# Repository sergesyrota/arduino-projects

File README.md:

arduino-projects
================

My projects and libraries with Arduino

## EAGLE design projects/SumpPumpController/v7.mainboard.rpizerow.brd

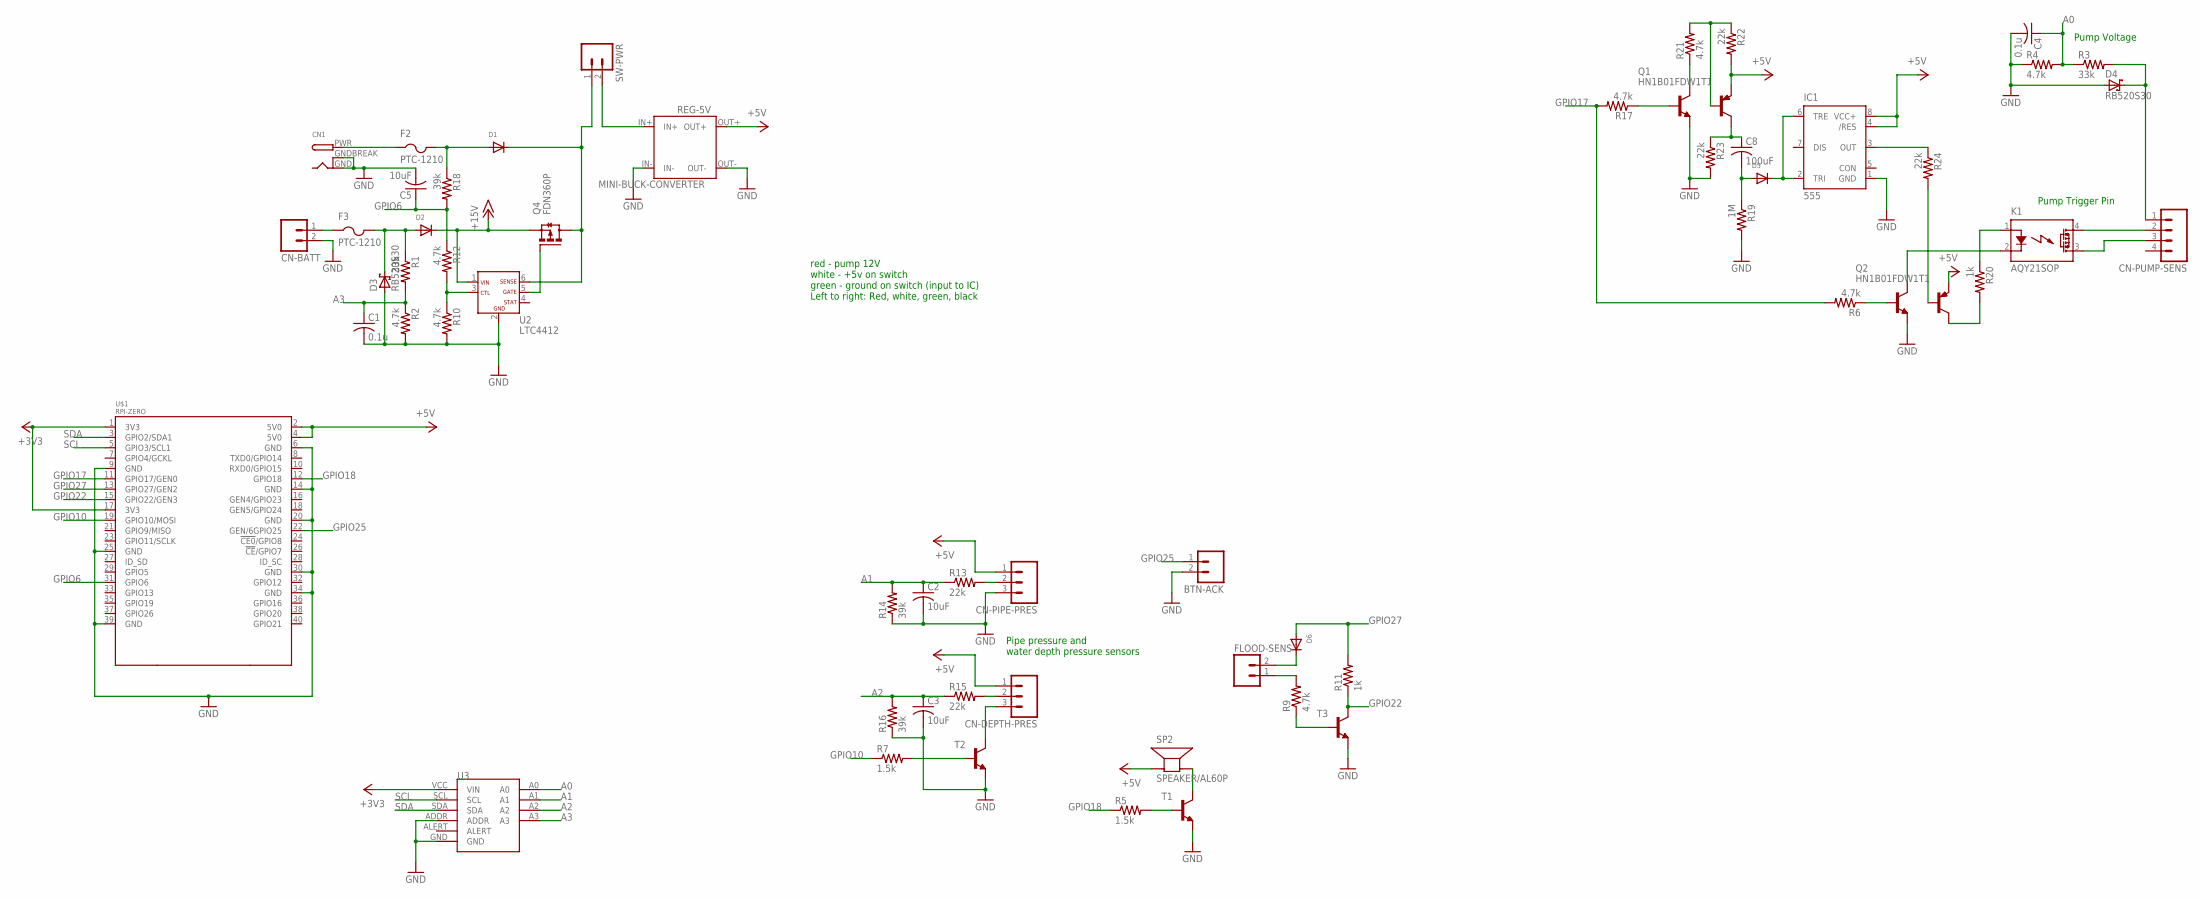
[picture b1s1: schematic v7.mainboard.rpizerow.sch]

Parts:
BTN-ACK: M02; 02P
C1, C4: 0.1u; C0603K
C2, C3, C5: 10uF; C0805K
C8: 100uF; C1210
CN1: DCBARRELPTH; DCJACK_2MM_PTH
CN-BATT: M02; 02P
CN-DEPTH-PRES: M03; 03P
CN-PIPE-PRES: M03; 03P
CN-PUMP-SENS: M04; 04P
D1, D2, D5, D6: DIODESOD-323F; SOD-323F
D3, D4: RB520S30; SOD523
F2, F3: PTC-1210; 1210
FLOOD-SENS: M02; 02P
IC1: 555; SO08
K1: AQY21SOP; SOP04
Q1, Q2: HN1B01FDW1T1; SOT23-6
Q4: FDN360P; SUPER-SOT3
R1, R3: 33k; R0603
R2, R4, R6, R9, R10, R12, R17, R21: 4.7k; R0603
R5, R7: 1.5k; R0603
R11, R20: 1k; R0603
R13, R15, R22, R23, R24: 22k; R0603
R14, R16, R18: 39k; R0603
R19: 1M; R0603
REG-5V: MINI-BUCK-CONVERTER
SP2: SPEAKER/AL60P; AL60P
SW-PWR: M02; 02P
T1, T2, T3: BC808-NPN-SOT23-BEC; SOT23-BEC
U2: LTC4412; SOT23-6
U3: GY-ADS1115THM; GY-ADS1115-THM
U$1: RPI-ZERO; RASPBERRYPI_BASTELSTUBE_V13_RASPI_BOARD_B+_FULL

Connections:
+3V3: U3.VCC (VIN), U$1.1 (3V3), U$1.17 (3V3)
+5V: CN-DEPTH-PRES.1, CN-PIPE-PRES.1, IC1.4 (/RES), IC1.8 (VCC+), Q1.1 (PNP-E), Q2.1 (PNP-E), R22.2, REG-5V.OUT+, SP2.1 (+), U$1.2 (5V0), U$1.4 (5V0)
+15V: D2.C, Q4.2 (S), U2.1 (VIN)
A0: C4.1, R3.1, R4.2, U3.A0
A1: C2.1, R13.1, R14.2, U3.A1
A2: C3.1, R15.1, R16.2, U3.A2
A3: C1.1, R1.2, R2.1, U3.A3
GND: BTN-ACK.2, C1.2, C2.2, C3.2, C4.2, C5.2, CN1.GND, CN1.GNDBREAK, CN-BATT.2, CN-PIPE-PRES.3, D3.2 (A), D4.2 (A), IC1.1 (GND), Q1.4 (NPN-E), Q2.4 (NPN-E), R2.2, R4.1, R10.2, R14.1, R16.1, R19.2, R23.2, REG-5V.IN-, REG-5V.OUT-, T1.E, T2.E, T3.E, U2.2 (GND), U3.ADDR, U3.GND, U$1.6 (GND), U$1.9 (GND), U$1.14 (GND), U$1.20 (GND), U$1.25 (GND), U$1.30 (GND), U$1.34 (GND), U$1.39 (GND)
GPIO6: C5.1, R12.1, R18.2, U$1.31 (GPIO6)
GPIO10: R7.1, U$1.19 (GPIO10/MOSI)
GPIO17: R6.2, R17.2, U$1.11 (GPIO17/GEN0)
GPIO18: R5.1, U$1.12 (GPIO18)
GPIO22: R11.1, T3.C, U$1.15 (GPIO22/GEN3)
GPIO25: BTN-ACK.1, U$1.22 (GEN/6GPIO25)
GPIO27: D6.A, R11.2, U$1.13 (GPIO27/GEN2)
unnamed: Q4.1 (G), U2.5 (GATE)
unnamed: R10.1, R12.2, U2.3 (CTL)
unnamed: SP2.2 (-), T1.C
unnamed: CN-PUMP-SENS.1, D4.1 (K), R3.2
unnamed: REG-5V.IN+, SW-PWR.2
unnamed: Q2.5 (NPN-B), R6.1
unnamed: CN-DEPTH-PRES.2, R15.2
unnamed: R5.2, T1.B
unnamed: CN-DEPTH-PRES.3, T2.C
unnamed: CN-PIPE-PRES.2, R13.2
unnamed: R9.1, T3.B
unnamed: Q1.5 (NPN-B), R17.1
unnamed: D2.A, D3.1 (K), F3.2, R1.1
unnamed: R7.2, T2.B
unnamed: CN-BATT.1, F3.1
unnamed: D1.C, Q4.3 (D), SW-PWR.1, U2.6 (SENSE)
unnamed: CN1.PWR, F2.1
unnamed: D1.A, F2.2, R18.1
unnamed: Q1.3 (NPN-C), R21.1
unnamed: FLOOD-SENS.1, R9.2
unnamed: D6.C, FLOOD-SENS.2
unnamed: K1.1 (A), R20.1
unnamed: Q1.2 (PNP-B), R21.2, R22.1
unnamed: C8.1, Q1.6 (PNP-C), R23.1
unnamed: C8.2, D5.A, R19.1
unnamed: D5.C, IC1.2 (TRI), IC1.6 (TRE)
unnamed: IC1.3 (OUT), R24.1
unnamed: K1.2 (K), Q2.3 (NPN-C)
unnamed: Q2.6 (PNP-C), R20.2
unnamed: Q2.2 (PNP-B), R24.2
unnamed: CN-PUMP-SENS.2, K1.4 (DS1)
unnamed: CN-PUMP-SENS.3, K1.3 (DS2)
SCL: U3.SCL, U$1.5 (GPIO3/SCL1)
SDA: U3.SDA, U$1.3 (GPIO2/SDA1)

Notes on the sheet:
Pump Voltage
Pump Trigger Pin
Pipe pressure and water depth pressure sensors
red - pump 12V white - +5v on switch green - ground on switch (input to IC) Left to right: Red, white, green, black

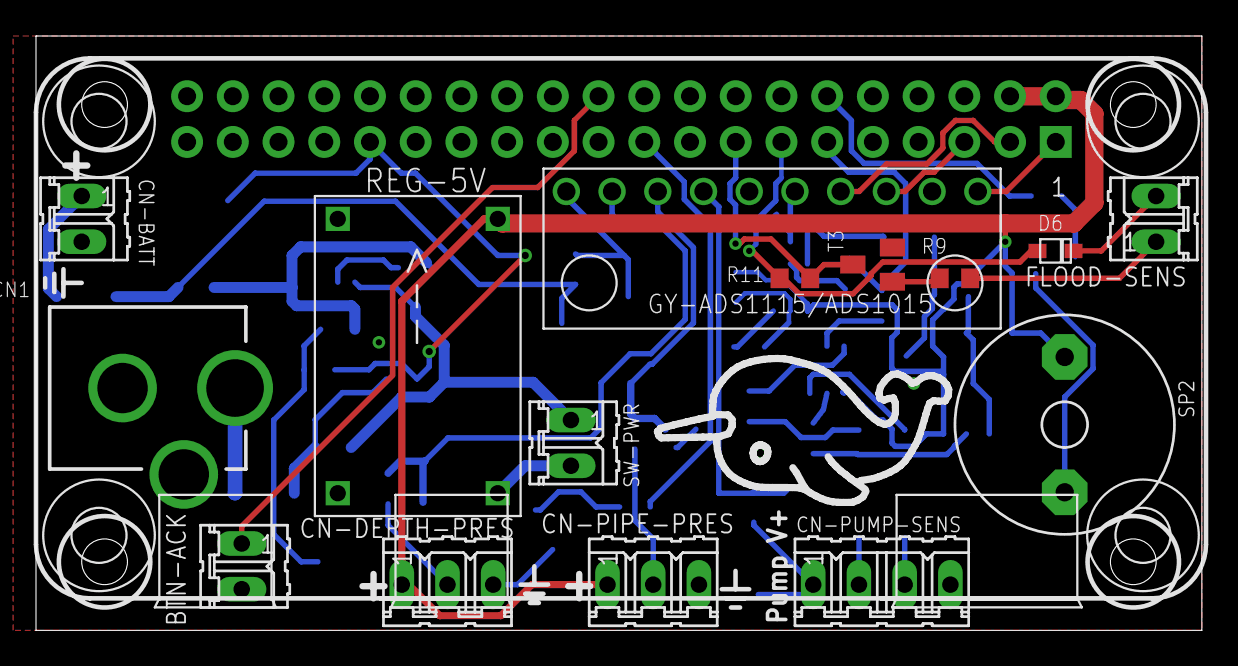
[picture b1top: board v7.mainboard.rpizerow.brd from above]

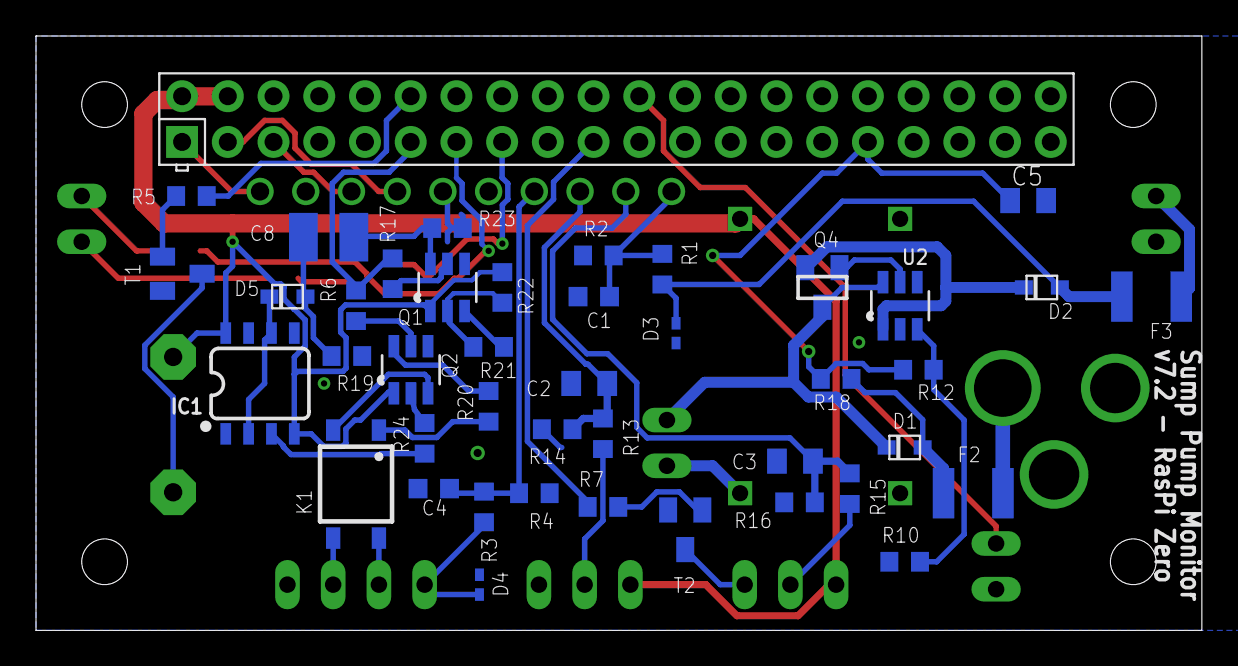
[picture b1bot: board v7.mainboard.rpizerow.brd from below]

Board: 2 copper layers, 64.8 x 33.0 mm, 58 parts (42 on the bottom side), 49 nets.

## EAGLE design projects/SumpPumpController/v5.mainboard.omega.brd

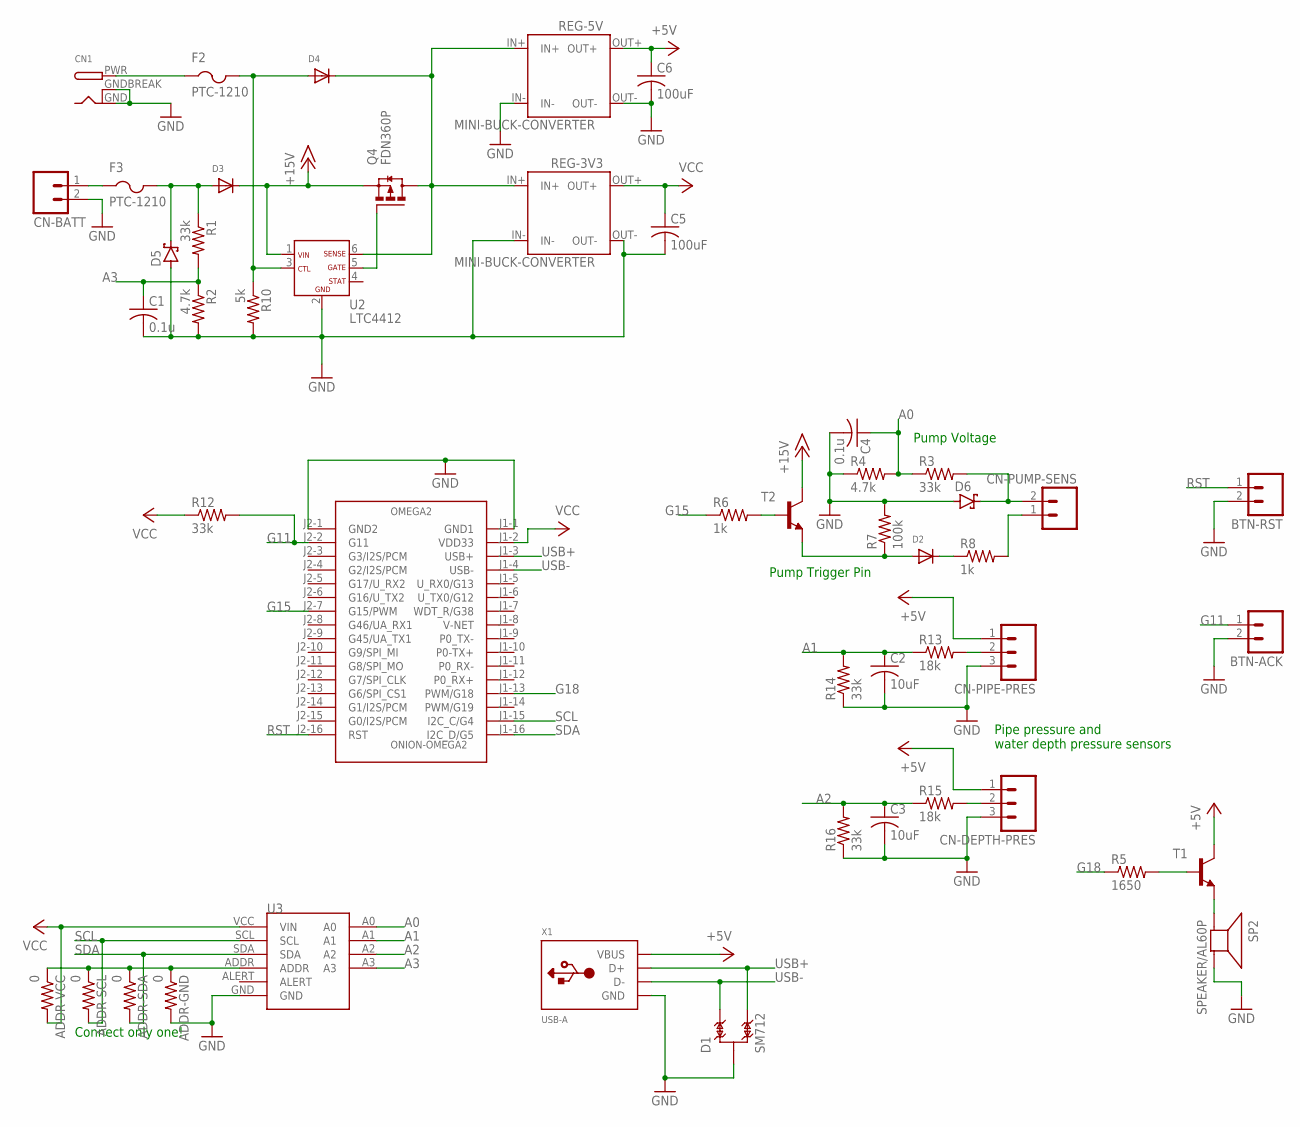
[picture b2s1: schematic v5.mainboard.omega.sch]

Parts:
ADDR-GND: 0; R0603
ADDR-SCL: 0; R0603
ADDR-SDA: 0; R0603
ADDR-VCC: 0; R0603
BTN-ACK: M02; 02P
BTN-RST: M02; 02P
C1, C4: 0.1u; C0603K
C2, C3: 10uF; C0805K
C5, C6: 100uF; C2220K
CN1: DCBARRELPTH; DCJACK_2MM_PTH
CN-BATT: M02; 02P
CN-DEPTH-PRES: M03; 03P
CN-PIPE-PRES: M03; 03P
CN-PUMP-SENS: M02; 02P
D1: SM712; SOT23-3
D2, D3, D4: DIODESMA; SMADIODE
D5, D6: SCHOTTKY-DIODESMC; SMC
F2, F3: PTC-1210; 1210
OMEGA2: ONION-OMEGA2; ONION-2MM-2X16
Q4: FDN360P; SUPER-SOT3
R1, R3, R12, R14, R16: 33k; R0603
R2, R4: 4.7k; R0603
R5: 1650; R0603
R6, R8: 1k; R0603
R7: 100k; R0603
R10: 5k; R0603
R13, R15: 18k; R0603
REG-3V3, REG-5V: MINI-BUCK-CONVERTER
SP2: SPEAKER/AL60P; AL60P
T1, T2: BC808-NPN-SOT23-BEC; SOT23-BEC
U2: LTC4412; SOT23-6
U3: GY-ADS1115THM; GY-ADS1115-THM
X1: USB-A; MOLEX_480371000

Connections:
+5V: C6.1, CN-DEPTH-PRES.1, CN-PIPE-PRES.1, REG-5V.OUT+, T1.C, X1.1 (VBUS)
+15V: D3.C, Q4.2 (S), T2.C, U2.1 (VIN)
A0: C4.1, R3.1, R4.2, U3.A0
A1: C2.1, R13.1, R14.2, U3.A1
A2: C3.1, R15.1, R16.2, U3.A2
A3: C1.1, R1.2, R2.1, U3.A3
G11: BTN-ACK.1, OMEGA2.J2-2 (G11), R12.2
G15: OMEGA2.J2-7 (G15/PWM), R6.1
G18: OMEGA2.J1-13 (PWM/G18), R5.1
GND: ADDR-GND.2, BTN-ACK.2, BTN-RST.2, C1.2, C2.2, C3.2, C4.2, C5.2, C6.2, CN1.GND, CN1.GNDBREAK, CN-BATT.2, CN-DEPTH-PRES.3, CN-PIPE-PRES.3, D1.3, D5.A, D6.A, OMEGA2.J1-1 (GND1), OMEGA2.J2-1 (GND2), R2.2, R4.1, R7.2, R10.2, R14.1, R16.1, REG-3V3.IN-, REG-3V3.OUT-, REG-5V.IN-, REG-5V.OUT-, SP2.2 (-), U2.2 (GND), U3.GND, X1.4 (GND)
unnamed: Q4.1 (G), U2.5 (GATE)
unnamed: ADDR-GND.1, ADDR-SCL.1, ADDR-SDA.1, ADDR-VCC.1, U3.ADDR
unnamed: CN-PUMP-SENS.2, D6.C, R3.2
unnamed: D2.C, R8.1
unnamed: CN-PUMP-SENS.1, R8.2
unnamed: CN-DEPTH-PRES.2, R15.2
unnamed: R5.2, T1.B
unnamed: SP2.1 (+), T1.E
unnamed: CN-PIPE-PRES.2, R13.2
unnamed: R6.2, T2.B
unnamed: D3.A, D5.C, F3.2, R1.1
unnamed: D2.A, R7.1, T2.E
unnamed: CN-BATT.1, F3.1
unnamed: D4.C, Q4.3 (D), REG-3V3.IN+, REG-5V.IN+, U2.6 (SENSE)
unnamed: CN1.PWR, F2.1
unnamed: D4.A, F2.2, R10.1, U2.3 (CTL)
RST: BTN-RST.1, OMEGA2.J2-16 (RST)
SCL: ADDR-SCL.2, OMEGA2.J1-15 (I2C_C/G4), U3.SCL
SDA: ADDR-SDA.2, OMEGA2.J1-16 (I2C_D/G5), U3.SDA
USB+: D1.1, OMEGA2.J1-3 (USB+), X1.3 (D+)
USB-: D1.2, OMEGA2.J1-4 (USB-), X1.2 (D-)
VCC: ADDR-VCC.2, C5.1, OMEGA2.J1-2 (VDD33), R12.1, REG-3V3.OUT+, U3.VCC (VIN)

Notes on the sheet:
Pump Voltage
Pump Trigger Pin
Pipe pressure and water depth pressure sensors
Connect only one!

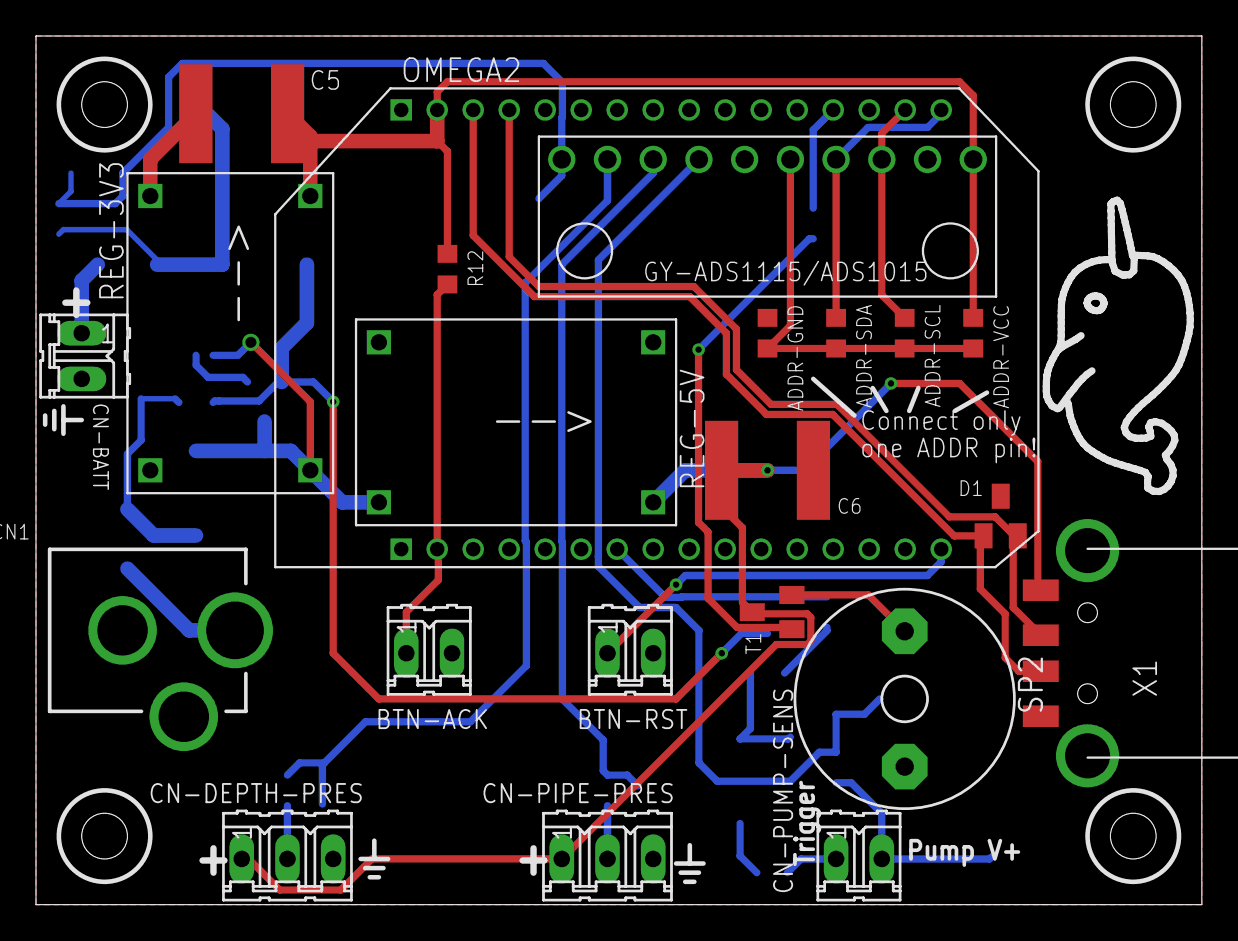
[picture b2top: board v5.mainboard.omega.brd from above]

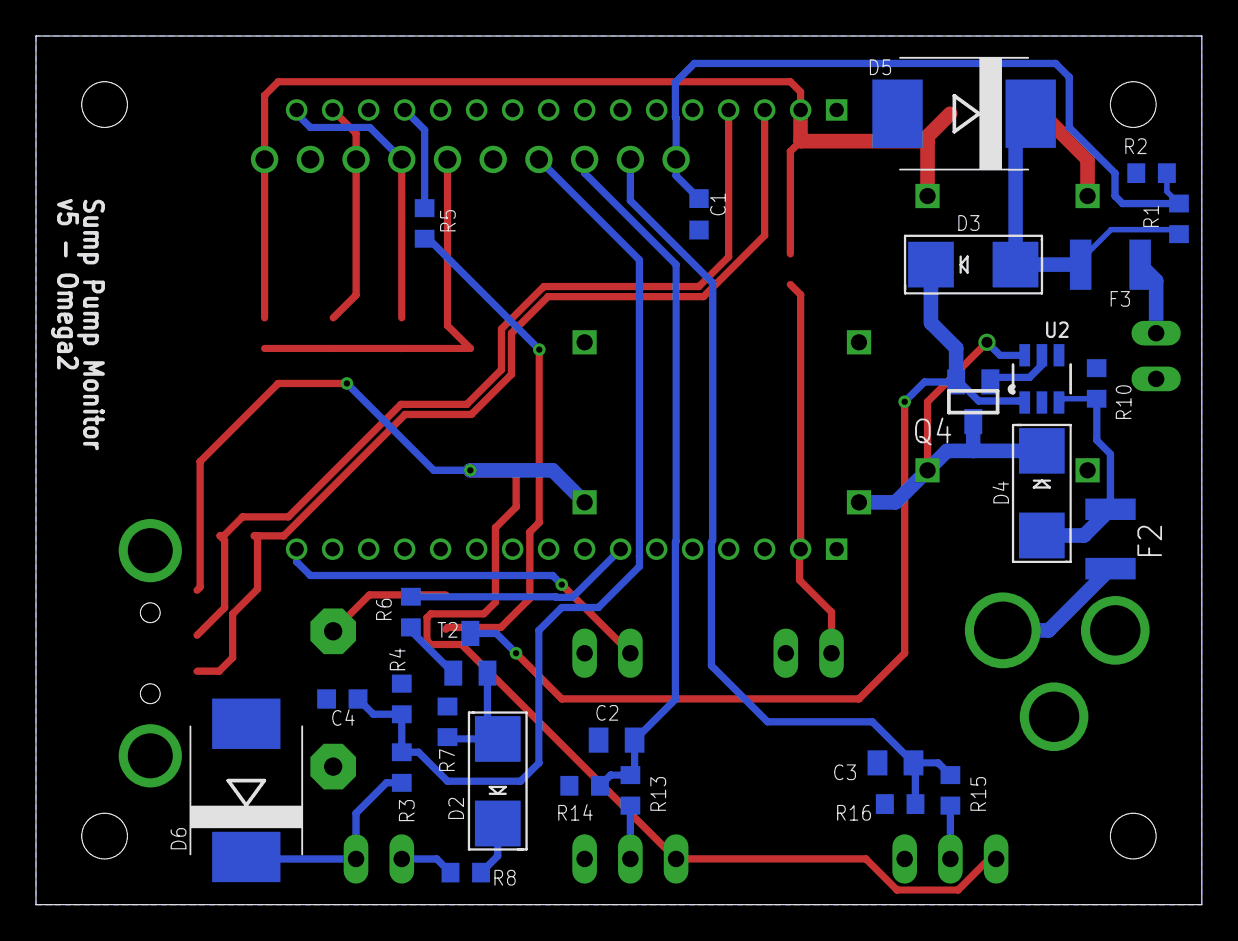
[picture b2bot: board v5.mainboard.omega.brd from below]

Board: 2 copper layers, 64.8 x 48.3 mm, 49 parts (27 on the bottom side), 32 nets.

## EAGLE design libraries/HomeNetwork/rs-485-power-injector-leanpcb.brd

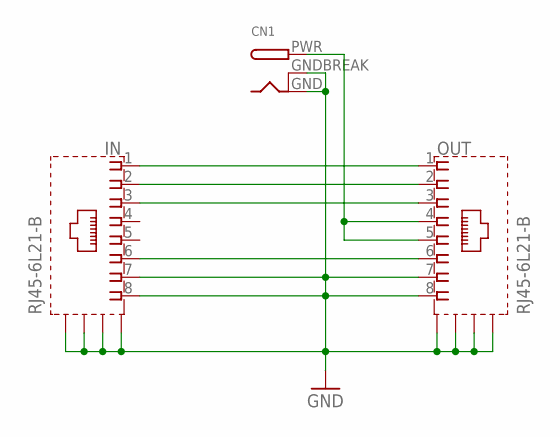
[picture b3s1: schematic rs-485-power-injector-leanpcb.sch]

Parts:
CN1: DCBARRELPTH; DCJACK_2MM_PTH
IN: RJ45-6L21-B; RJ45-SHIELD1
OUT: RJ45-6L21-B; RJ45-SHIELD1

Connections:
GND: CN1.GND, CN1.GNDBREAK, IN.7, IN.8, IN.S1 (S), IN.S2 (S), IN.S3 (S), IN.S4 (S), OUT.7, OUT.8, OUT.S1 (S), OUT.S2 (S), OUT.S3 (S), OUT.S4 (S)
unnamed: IN.1, OUT.1
unnamed: IN.2, OUT.2
unnamed: IN.3, OUT.3
unnamed: IN.6, OUT.6
unnamed: CN1.PWR, OUT.4, OUT.5

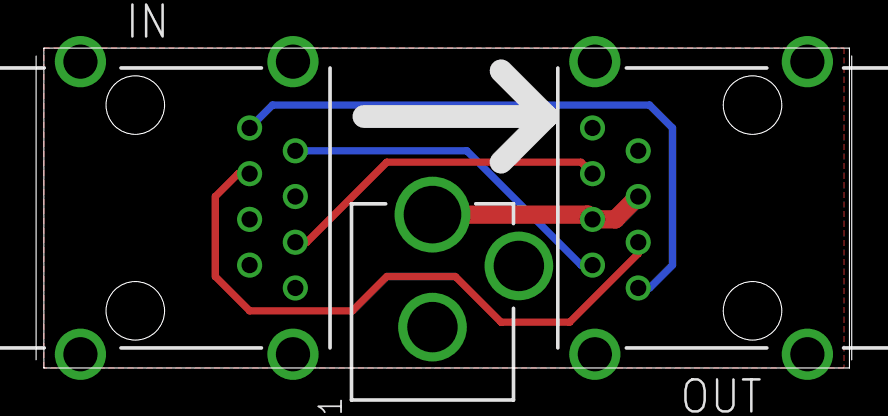
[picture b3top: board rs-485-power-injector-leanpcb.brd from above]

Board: 2 copper layers, 45.3 x 17.8 mm, 3 parts (0 on the bottom side), 6 nets.

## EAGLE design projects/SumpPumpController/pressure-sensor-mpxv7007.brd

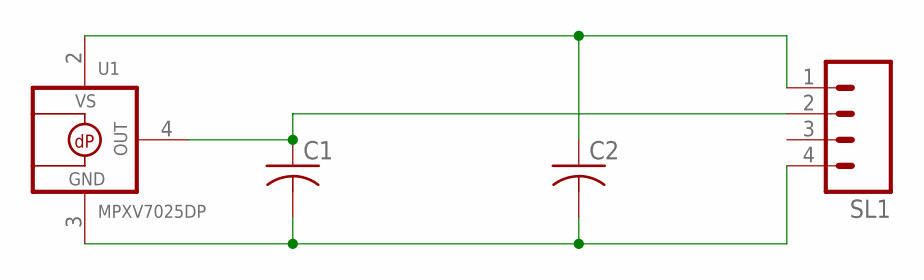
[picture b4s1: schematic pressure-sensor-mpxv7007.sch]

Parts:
C1: C-USC0805; C0805
C2: C-USC0603; C0603
SL1: M04; 04P
U1: MPXV7025DP; SOP8-1351

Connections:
GND: C1.2, C2.2, SL1.4, U1.3 (GND)
unnamed: C2.1, SL1.1, U1.2 (VS)
unnamed: C1.1, SL1.2, U1.4 (+VOUT)

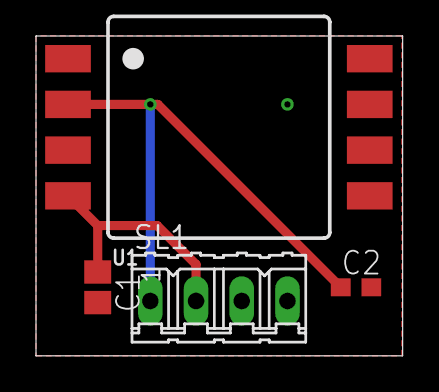
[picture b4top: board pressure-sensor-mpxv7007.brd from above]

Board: 2 copper layers, 20.4 x 17.8 mm, 4 parts (0 on the bottom side), 3 nets.

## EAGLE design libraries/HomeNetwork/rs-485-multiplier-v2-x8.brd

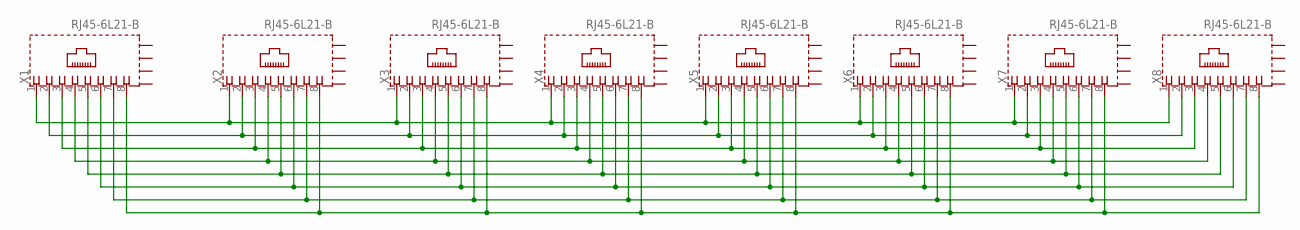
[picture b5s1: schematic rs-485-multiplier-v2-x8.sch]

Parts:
X1, X2, X3, X4, X5, X6, X7, X8: RJ45-6L21-B; RJ45-SHIELD1

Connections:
unnamed: X1.1, X2.1, X3.1, X4.1, X5.1, X6.1, X7.1, X8.1
unnamed: X1.2, X2.2, X3.2, X4.2, X5.2, X6.2, X7.2, X8.2
unnamed: X1.3, X2.3, X3.3, X4.3, X5.3, X6.3, X7.3, X8.3
unnamed: X1.4, X2.4, X3.4, X4.4, X5.4, X6.4, X7.4, X8.4
unnamed: X1.5, X2.5, X3.5, X4.5, X5.5, X6.5, X7.5, X8.5
unnamed: X1.6, X2.6, X3.6, X4.6, X5.6, X6.6, X7.6, X8.6
unnamed: X1.7, X2.7, X3.7, X4.7, X5.7, X6.7, X7.7, X8.7
unnamed: X1.8, X2.8, X3.8, X4.8, X5.8, X6.8, X7.8, X8.8

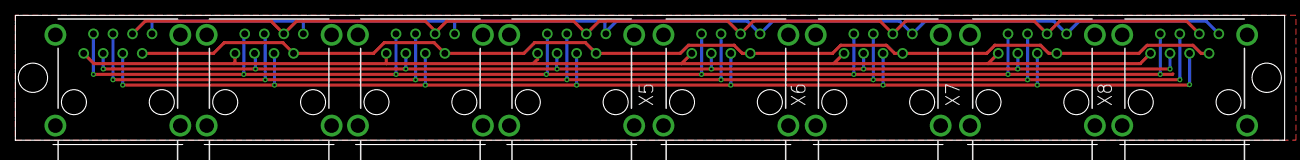
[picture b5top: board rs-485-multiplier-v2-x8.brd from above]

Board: 2 copper layers, 165.1 x 16.8 mm, 8 parts (0 on the bottom side), 8 nets.

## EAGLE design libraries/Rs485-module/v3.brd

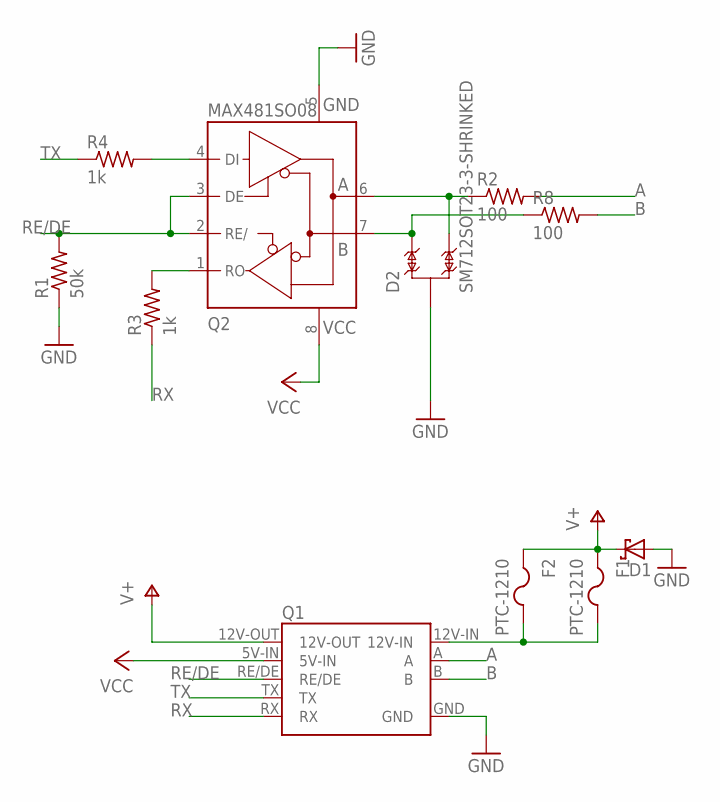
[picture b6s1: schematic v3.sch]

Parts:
D1: SCHOTTKY-DIODESMC; SMC
D2: SM712SOT23-3-SHRINKED; SOT23-3-SHRINKED
F1, F2: PTC-1210; 1210
Q1: RS485-ADAPTER0.05-CONNECTOR; RS485-ADAPTOR-05
Q2: MAX481SO08; SO08
R1: 50k; R0603
R2, R8: 100; R0603
R3, R4: 1k; R0603

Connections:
12V-IN: F1.2, F2.2, Q1.12V-IN
A: Q1.A, R2.2
B: Q1.B, R8.2
GND: D1.A, D2.3, Q1.GND, Q2.5 (GND), R1.1
unnamed: D2.2, Q2.7 (B), R8.1
unnamed: Q2.1 (RO), R3.2
unnamed: Q2.4 (DI), R4.2
unnamed: D2.1, Q2.6 (A), R2.1
RE/DE: Q1.RE/DE, Q2.2 (RE/), Q2.3 (DE), R1.2
RX: Q1.RX, R3.1
TX: Q1.TX, R4.1
V+: D1.C, F1.1, F2.1, Q1.12V-OUT
VCC: Q1.5V-IN, Q2.8 (+5V)

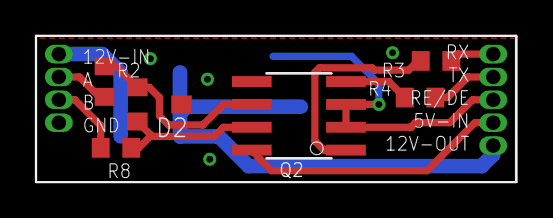
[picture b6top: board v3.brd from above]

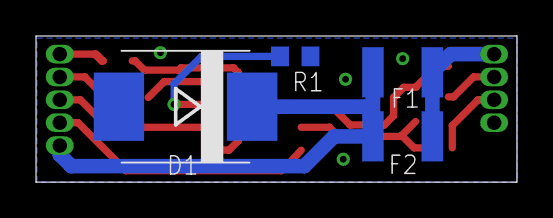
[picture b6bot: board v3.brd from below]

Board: 2 copper layers, 26.7 x 8.1 mm, 11 parts (4 on the bottom side), 13 nets.

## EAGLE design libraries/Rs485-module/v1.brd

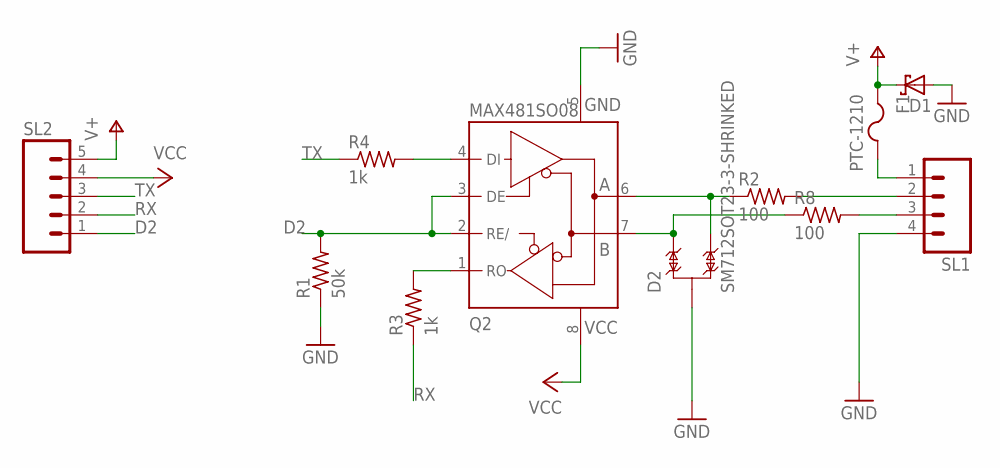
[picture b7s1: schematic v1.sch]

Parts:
D1: SCHOTTKY-DIODESMC; SMC
D2: SM712SOT23-3-SHRINKED; SOT23-3-SHRINKED
F1: PTC-1210; 1210
Q2: MAX481SO08; SO08
R1: 50k; R0603
R2, R8: 100; R0603
R3, R4: 1k; R0603
SL1: M04; 04P
SL2: M05; 05P

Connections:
D2: Q2.2 (RE/), Q2.3 (DE), R1.2, SL2.1
GND: D1.A, D2.3, Q2.5 (GND), R1.1, SL1.4
unnamed: F1.2, SL1.1
unnamed: D2.2, Q2.7 (B), R8.1
unnamed: Q2.1 (RO), R3.2
unnamed: Q2.4 (DI), R4.2
unnamed: R8.2, SL1.3
unnamed: R2.2, SL1.2
unnamed: D2.1, Q2.6 (A), R2.1
RX: R3.1, SL2.2
TX: R4.1, SL2.3
V+: D1.C, F1.1, SL2.5
VCC: Q2.8 (+5V), SL2.4

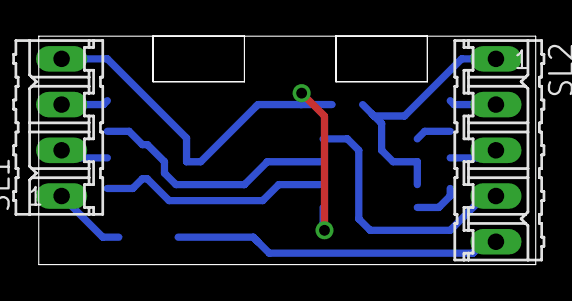
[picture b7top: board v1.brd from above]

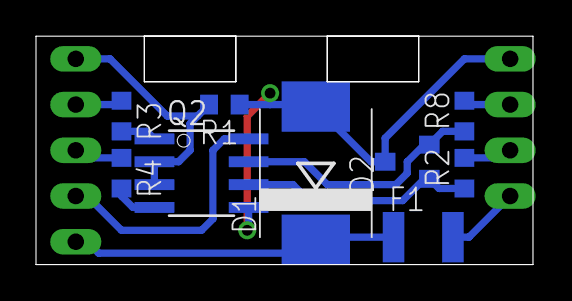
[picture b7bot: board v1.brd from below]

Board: 2 copper layers, 27.6 x 12.7 mm, 11 parts (9 on the bottom side), 13 nets.

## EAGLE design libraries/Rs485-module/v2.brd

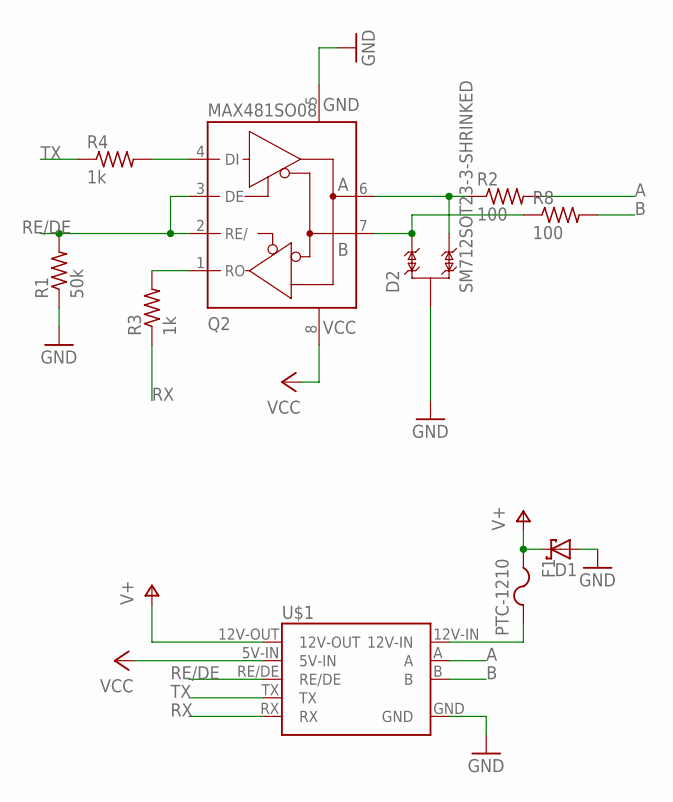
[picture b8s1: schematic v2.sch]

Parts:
D1: SCHOTTKY-DIODESMC; SMC
D2: SM712SOT23-3-SHRINKED; SOT23-3-SHRINKED
F1: PTC-1210; 1210
Q2: MAX481SO08; SO08
R1: 50k; R0603
R2, R8: 100; R0603
R3, R4: 1k; R0603
U$1: RS485-ADAPTER; RS485-ADAPTOR

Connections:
12V-IN: F1.2, U$1.12V-IN
A: R2.2, U$1.A
B: R8.2, U$1.B
GND: D1.A, D2.3, Q2.5 (GND), R1.1, U$1.GND
unnamed: D2.2, Q2.7 (B), R8.1
unnamed: Q2.1 (RO), R3.2
unnamed: Q2.4 (DI), R4.2
unnamed: D2.1, Q2.6 (A), R2.1
RE/DE: Q2.2 (RE/), Q2.3 (DE), R1.2, U$1.RE/DE
RX: R3.1, U$1.RX
TX: R4.1, U$1.TX
V+: D1.C, F1.1, U$1.12V-OUT
VCC: Q2.8 (+5V), U$1.5V-IN

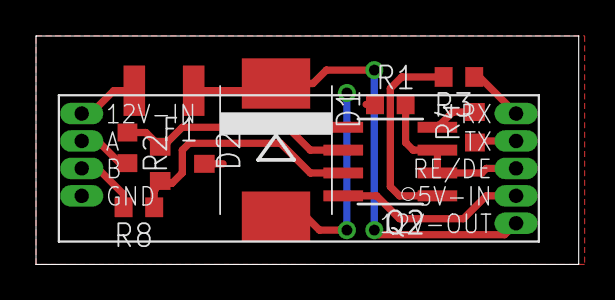
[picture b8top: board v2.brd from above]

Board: 2 copper layers, 30.1 x 12.7 mm, 10 parts (0 on the bottom side), 13 nets.

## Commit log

2013-07-21 Adding AutoHeadlights library
2013-07-21 Added notes on hardware components
2013-07-21 Added OneTouchLaneChange library
2013-07-21 Added my auto lights and one touch turn signal Arduino sketch
2013-07-23 Added readme to OneTouchLaneChange library
2013-08-03 Adding first draft of automated bath fan sketch, and humidity check class
2013-08-03 Cleaned up, added motion sensor support, implemented dummy reader for the switch
2013-08-04 Added data logger functionality
2013-08-14 Spelling correction for DHT11
2013-08-14 Bug fixes and adjustments based on field test
    - Fixed a bug that caused SD module to fail writing when trying to do so
    in constructor, before setup() is called (just removed header line
    check)
    - Changed triggeredHumidity check to short term average, as long term is
    too slow, and most likely we will not get back to that level fast enough
    - Added temperature in the log output
2013-08-15 Adjusted fail safe to 4 hours
2013-08-18 Adjusted headlight trigger values and time. Removed default overrides
2013-11-30 Adding Proximity sensor by device name
2013-11-30 Updates to proximity sensor
    Updated address storage method
    Removed debug serial output
    Delaying repeat ping if device is currently in range to avoid constant
    communication
2014-05-21 Adding sump pump controller files to the repo
2014-05-21 Renamed self test into controller in preparation of offloading all that logic there
2014-05-22 Updated instrumentation schematic to include voltage divider on the reference pin
2014-05-22 Added water main project
2014-05-23 Added pressure sensor functionality to the system, and changed from pump cycle reporting to number of seconds it was ON. Also added back self test, and added 24 hour minimum constraint.
2014-05-24 Adding automation protocol library v1
2014-05-24 Adding water main connection board
2014-05-24 Fixing a bug where when AC pump was ON when status was requested produced unexpected results (adding millis to seconds)
2014-05-26 Bug fixing in sump pump project: * Sending responses after action commands * Adding now() time to debug response * fixing long issues with self test time calculations * Delaying water level measureme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
2014-05-28 Added more debug output Adjusted instrumentation amplifier circuit to inlude ~1Hz filter, as turbulence in the sensor triggers false positives; Fixed a bug where self test time was not accounted for 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
2014-05-28 Added text to schematic for color coding of controll wire connection (WaterMain project)
2014-05-28 Starting to put together a tepmlate for Atmel based boards
2014-05-30 Adding first draft of WaterMain project
2014-05-30 Adding monitoring for when AC pump is on for too long to the sump pump project.
2014-06-01 Cleanup unused files in sump pump controller project.
2014-06-01 Added RS-485 splitter/multiplier board to the library
2014-06-02 Adjusted RS-485 splitter to ignore mounting holes to make room for routes
2014-06-03 Finished schematic of basic Atmel template. Kept all components but microcontroller out, as each board will have its own requirements, plus it would be challenging to keep all pieces from bumping int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
2014-06-08 Raising baud rate on the bus to max that ceramic resonator can reliably handle
2014-07-05 v1 of CPU module board finished
2014-07-07 Adding water meter counter and unit tests
2014-07-07 Moved unit tests into a sub-directory, hopefully they will not interfere with Arduino IDE build now.
2014-07-07 Just the counter version of water main code
2014-07-12 Added v2 of rs-485 multiplier board
2014-07-21 Finished v1 version of the board. Figured out that I have no way to control the valve from sensor. Built a fix-board to alleviate that issue. Just in case, threw down v2 with all components, but not 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
2014-07-21 Added config file to Water main, and moved analog sensor to that file as well.
2014-07-21 Added setup steps for valve directive pins, and fixed open/close pin mixup.
2014-07-27 Added valve control commands to water main project
2014-11-04 Added water main remote connection board v2 (with temperature and water leak probes)
2014-11-04 Updated water main sketch to add new v2 board, along with temperature and humidity probes.
2014-11-05 Refactored duplicate handling of errors in climate sensors for water meter module
2014-11-30 Updated PCB for CPU, increasing drill holes for some of the pins.
2014-11-30 Updated water main config, as valve connections got swapped
2014-11-30 Starting new project: bedroom HVAC balancer. Initial commit with first 2 versions of processing board
2014-11-30 Added kitchecn environment monitoring project
2014-11-30 Adding auto-led-light project in bedroom (to turn on LEDs after sunset
2014-12-21 Built hvac module, wireless probes, room controller boards. Wrote sketches for wireless probe, and some for AC sensors (still not tested, missing a few sensors themselves)
2014-12-21 Adding Pro Mini programmer shield
2014-12-21 Adding nrf24l01 bridge to rs485
2015-02-27 Added support for passing parameters to devices in the form of assertCommandStarts. This returns the rest of the command to be processed by the application.
2015-02-27 Adding explicit DHT22 to remote sensors RF module, and adding all sensor addresses to ac sensors.
2015-02-27 Adding power blinds project files.
2015-03-06 Adding v4 of sump pump controller. Includes standard Arduino Pro Mini connection, as well as few layers of protection. Although the drawing has a mistake, as cutout has wrong orientation :(
2015-03-06 Adjusted sump pump Arduino sketch for the new v4 board. TODO: fix reset alert handling; add butn-ack handling; implement eeprom configuration; re-enable buzzer pin; add last alert to memory (e.g. whe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
2015-03-06 Power blinds: adjusted to 9600 baud, added motor stop logic, added optical sensors readout. TODO: improve EEPROM storage; make baud rate adjustable; implement motion sensor; implement light sensor;
2015-03-07 Added improved alert handling, as well as ACK button to silence them. Alerts are now ranked in the order of priority. TODO: implement EEPROM configuration; re-enable buzzer pin.
2015-03-09 Sump pump controller: Moved more pins to include file; implemented EEPROM config; implemented config adjustment through rs485; Moved all sprintf templates into PROGMEM. TODO: enable buzzer when this 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
2015-03-09 Sump pump controller: changed serial interface to take baud rate from config.
2015-03-11 Added buzzer pin enable to config. Changed back from PROGMEM to standard variables for hardcoded text, as something was not working at all for most of those.
2015-03-13 Power Blinds: added configuration to dining controller, finished up controller logic
2015-03-14 Power blinds: updated dining controller to add optical sensor stop delay, switched to config baud rate, instead of hardcoded, fixed a bug with switch reading.
2015-03-14 Power blinds: refactoring dining controller to work off of proximity sensor only (without a need for tape marking); increased max configurable motor runtime.
2015-03-14 Power blinds: fixing config version increase...
2015-03-14 Power blinds: switched dining controller to differential reading, instead of proximity (for top position sensing). Adjusted defaults. switched to external pull-up.
2015-03-15 Power blinds: fixed a bug with knownBlindsPosition that was not allowing reversal of motion because known position was not reset when we start rolling
2015-03-15 Power blinds: adding external pull-up resistors for inputs, and adding TVS diode for RS-485
2015-03-15 Power blinds: Adjusted rollDown blinds threshold for dining controller.
2015-04-08 Fixing random hanging issues when rolling down the blinds
2015-04-26 Added getPressure command and fixed distance reading bug in SUmp Pump system.
2015-04-26 Added protection diode to motor control module in Power Blinds.
2015-04-26 Adjusting serial speed to 9600 for water main sensors.
2015-04-26 Adding nrf24l01 shield to the library
2015-04-26 Adjusted speed to 9600, and updated net address to be taken from confid, in HVAC balancer project.
2015-07-11 Adding RS-485 module board (including full protection circuit)
2016-02-09 Restored back/forward annotation of v3
2016-02-09 Modified v3 for large drill size (so that pin header actually fits) and adjusted labels to make sure they are readable once board is produced.
2016-03-16 Add vent control implementation
2016-03-16 Fixed SyrotaAutomation library indentation
2018-10-23 Adding 8-port RS485 multiplier board
2019-02-02 Adding gitignore for eagle
2019-02-02 Changing sump pump to laser sensor a while ago. No workie
2019-02-02 Adding pressure sensor board
2019-02-02 Adding RS-485 connector boards.
2019-02-02 Changing depth reading sensor to pressure-based
2019-02-02 Converted most other strings to program memory (requires SyrotaAutomation library update)
2019-02-02 Updating SyrotaAutomation to support progmem strings with const char arguments.
2019-02-10 Added dc pump status, and dc pump overload alert
2019-02-13 Debugging
2019-02-13 Revert "Converted most other strings to program memory (requires SyrotaAutomation library update)"
    This reverts commit 6352d9a9bb002631ecab05c55ee7798ea051c195.
2019-02-13 Reverting PSTR changes, seems something's wrong.
2019-02-14 Removing all other progmem from sump pump as it's all messed up with responses, not able to get strings from the right place.
2019-02-14 Another attempt at progmem
2019-02-14 Revert "Another attempt at progmem"
    This reverts commit 48001d9101a8e1818950a74bfce222043c852254.
2019-02-14 Reverting progmem again. Compiles successfully, but responses are garbage
2019-02-14 Adjusting some defaults after testing production deployment :)
2024-08-14 Misc updates
2024-08-14 Extra board drawings
2024-08-14 Adding AC pump pressure hysterisis so it doesn't flap on and off all the time.
2024-08-14 Type + time lib update, and some new defaults

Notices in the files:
parts and their libraries:
SparkFun-IC-Special-Function: Licensing: Creative Commons ShareAlike 4.0 International - https://creativecommons.org/licenses/by-sa/4.0
